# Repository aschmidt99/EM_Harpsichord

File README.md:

# NOTE: This repo is outdated!
Hello! While this repository still covers the basics of Lorentz Force Actuation and feedback, a more comprehensive and curated version can be found on this newer repository: [Sparksichord Project](https://github.com/aschmidt99/Sparksichord_NIME2025)

# Electromagnetic Harpsichord

The EM Harpsichord is an augmented harpsichord that uses optical sensors, audio power amplifier chips, and some simple signal processing to sustain the vibrations of its brass strings. This early prototype uses one circuit board for every string you wish to sustain. A work-in-progress performance/demonstration was given on October 2nd, 2023 at the 63rd Annual University of Michigan Organ Conference. For this demonstration, 3 strings had optical sustaining enabled and 8 strings had audio-playback enabled.

## Video Examples
Here is a [selection of audio examples](https://drive.google.com/drive/folders/1B2c4qz-7Rl1Y2wPH64m0Ud0_MTGL74a2?usp=sharing) of both sustainers and audio playback through the harpsichord strings.

## Working Principle
This simple board uses a ITR20403 Optical Photo-interrupt to sense the vibrations (position) of a harpsichord string. The derivative of this signal is amplified and sent to a 5-Watt audio amplifier chip (PAM8406) that is normally used to power small 4 or 8 ohm speakers. Rather than connect to a speaker, the output terminals of the speaker chip are connected to each end of one of the strings on a harpsichord. The amplified signal pushes current through the string, which generates an alternating magnetic field that interacts with a strong magnetic field from permanent neodymium magnets.

The working principle is similar to the more familiar eBow, but rather sensing and inducing vibrations with electromagnetic coils, we sense with an optical sensor and actuate with Lorentz force actuation.

## Simple System Diagram

This is the signal flow for the sustainer circuit in each board. You need one circuit board for each string you wish to sustain.

## The Circuit Board

The circuitboard is thin enough to fit between the harpsichord's strings. We mounted them to an aluminum extrusion C Beam with slide nuts, M4 screws, and some small 3D printed brackets.

## How to order
### JLCPCB
If you wish to have this exact board, you can order these circuit boards from JLCPCB by uploading GERBER-EMHarpsichord_Sustainer+Playback.zip to JLCPCB. Also upload BOM-EMHarpsichord_Sustainer+Playback.csv and CPL-EMHarpsichord_Sustainer+Playback.csv to have JLCPCB assemble the board for you.
(Note: Double check the orientation of each IC in JLCPCB. They are often incorrect by default.)

### Reach out to me
Alternatively, reach out to me (schmia@umich.edu) in case I have some extra :)

### Other board house
If you are familiar with a different board house, feel free to export as you usually would from KiCad.

### Notes before ordering/assembling
If you order based on my files, the optical sensor will be placed on the wrong side of the board. I found it easier to source the components from JLCPCB and desolder/resolder the ITR20403 to the other side of the board. If you can find them for cheap elsewhere, it would probably save you a small headache to order them separately and omit them from the board when ordering.

## How to use
### Wiring up
- A 3 Pin JST XH 2.54mm connector supplies 5V, Ground, and an auxiliary audio input. If you don't anticipate using audio playback, simply wire up the 5V and Ground and you are good to go. Chain several boards together to sustain multiple notes. We put a SPST switch between each board's ground and the power supply ground to allow us to select which strings were activated individually.
- The PAM8406 chip is advertised to support 4-8 ohm loads, though the data sheet notes that it can support loads down to 2 ohms. The data sheet also notes that outputs of the PAM8406 amplifier chip have built in short circuit protection, and the outputs will not activate if they detect less than 2 ohm load. Therefore, you must ensure that there are at least 2 ohms between the (+) and (-) terminal of each speaker output.
	- Most of the brass strings on our harpsichord measured much less than 1 Ohm, so we opted to put a 2-Ohm 10W Power Resistor between each string and one of the terminals the selected channels.

### Magnets
- To induce vibration, the strings must be exposed to a strong magnetic field. We have been using N52 neodymium magnets (purchased from kjmagnetics.com) for this purpose. The strength of the vibration is proportional to the strength of the magnetic field, and although the presence of just one or two magnets usually is enough to get sound going, more magnets seems to encourage a higher acoustic output.
- The orientation of the magnet does matter. Flip the magnet back and forth to determine which side is inducing the sound you like. One side should sustain the fundamental frequency of the string and the other may damp the fundamental while favoring odd harmonics.
- If you wish to use multiple magnets on a string, you will most likely want all of their poles pointed in the same direction, although interesting magnet placement can yield interesting results...

### Channels
- The 'left' output channel of the board is connected to the optical sensor, which creates a closed feedback loop to sustain vibrations on the connected string.
- The 'right' output channel of the board amplifies an auxiliary input signal.

### Additional Notes:
- The optical sensor needs to be placed very precisely over the string to ensure it picks up the vibration. The sensing range of the string is very small and is easy to clip. You can use an oscilloscope on test point 1 (TP1) to make sure the sensor isn't clipping before the gain stage.
- If it is clipping (and you do not like the output tone), consider moving the sensor board closer to a termination point of the string where its range of vibration is much smaller. This should yield a smoother sustaining sound.
- The feedback loop is very sensitive to the position of the sensor. You will likely notice timbral changes as you change the point on the string where the sensor is located, the position of the sensor over the string, and the positions of the magnets.
- Bar magnets induce stronger vibrations than cylindrical with the same pull force.
- The resistance of a metal string is a function of its material, gauge, length, and temperature. The higher the resistance, the more apt the string is to detuning. If your strings are detuning too much, try using a thicker wire, more conductive material, or lower current. If you are building a new instrument rather than augmenting an existing one, try different string lengths.

## Design References
- the 'RelevantDocuments' folder holds data sheets and some blog/forum posts I found helpful while designing the board. (Dave Corsie's blog)[https://www.davecorsie.com/optical-pickup-blog] helped me figure out how to design the optical pickup circuit and the DIYAudio blog helped me make a better PCB layout for the PAM8406 Chip.

## Future Improvements
### Support Loads < 2 Ohms
One of the most obvious shortcomings of this system is the wasted power. If a given string is only 0.2 Ohms and we compensate with a 2 Ohm resistor, most (~90%) of the power is being dissipated as heat through the resistor rather that contributing towards generating vibrations. I suspect looking into circuits that are anticipating extremely low loads such as ribbon speaker amplifiers will be a worthwhile endeavor and likely be a solution for the next version of this circuit.

### Lower Heat Buildup
On the other hand, the large dummy load ensures the majority of the power is dissipated somewhere other than the string, which prevents heat buildup (and thus detuning) in the string. The magnetic field generated by the string is proportional to current only - it does not factor in voltage. Therefore, an alternative system improvement may be to increase string gauges to /decrease/ overall resistance and continue to utilize the power resistors.

### Controlled Detuning
With more advanced feedback control, it may be possible to control how much or little each string is detuned during actuation. This could allow the performer to change tuning systems rapidly and on-the-fly - a process that usually takes considerable time and attention.

### Sustainer on every string
A natural progression for the project is to add a sustainer board for every string so that we can sustain any strings rather than just the few we chose for our work-in-progress demonstration. A double-manual harpsichord might work well, where one manual controls the sustainers and the other moves jacks and plucks the strings as usual.

### Sensing the keys
In the next version of this project, we aim to actively sense the position of each harpsichord key to use as a control signal for the sustainer of each corresponding string. Mechanically separating the harpsichord keys from the strings will allow us to map and re-map the interaction between key presses and actuation however we wish.

## Acknowledgements
- This project was enabled by Professor Joseph Gascho, Associate Professor of Music and Director of the Stearns Collection at the University of Michigan Ann Arbor.
- This project was inspired by the (Electromagnetic Resonator Piano)[http://instrumentslab.org/research/mrp.html], a project by Andrew McPherson at the Augmented Instruments Lab.
- Additional inspiration and insight was provided by (Techniques and Circuits for Electromagnetic Instrument Actuation)[https://www.nime.org/proceedings/2012/nime2012_117.pdf] by Andrew McPherson (see Section 2.4 - Lorentz Force Sustaining).

## Software Versions used
- KiCad (6.0.7-1)-1 for MaxOS Version 13.4.1
- LTSpice 17.0.40 for OS X

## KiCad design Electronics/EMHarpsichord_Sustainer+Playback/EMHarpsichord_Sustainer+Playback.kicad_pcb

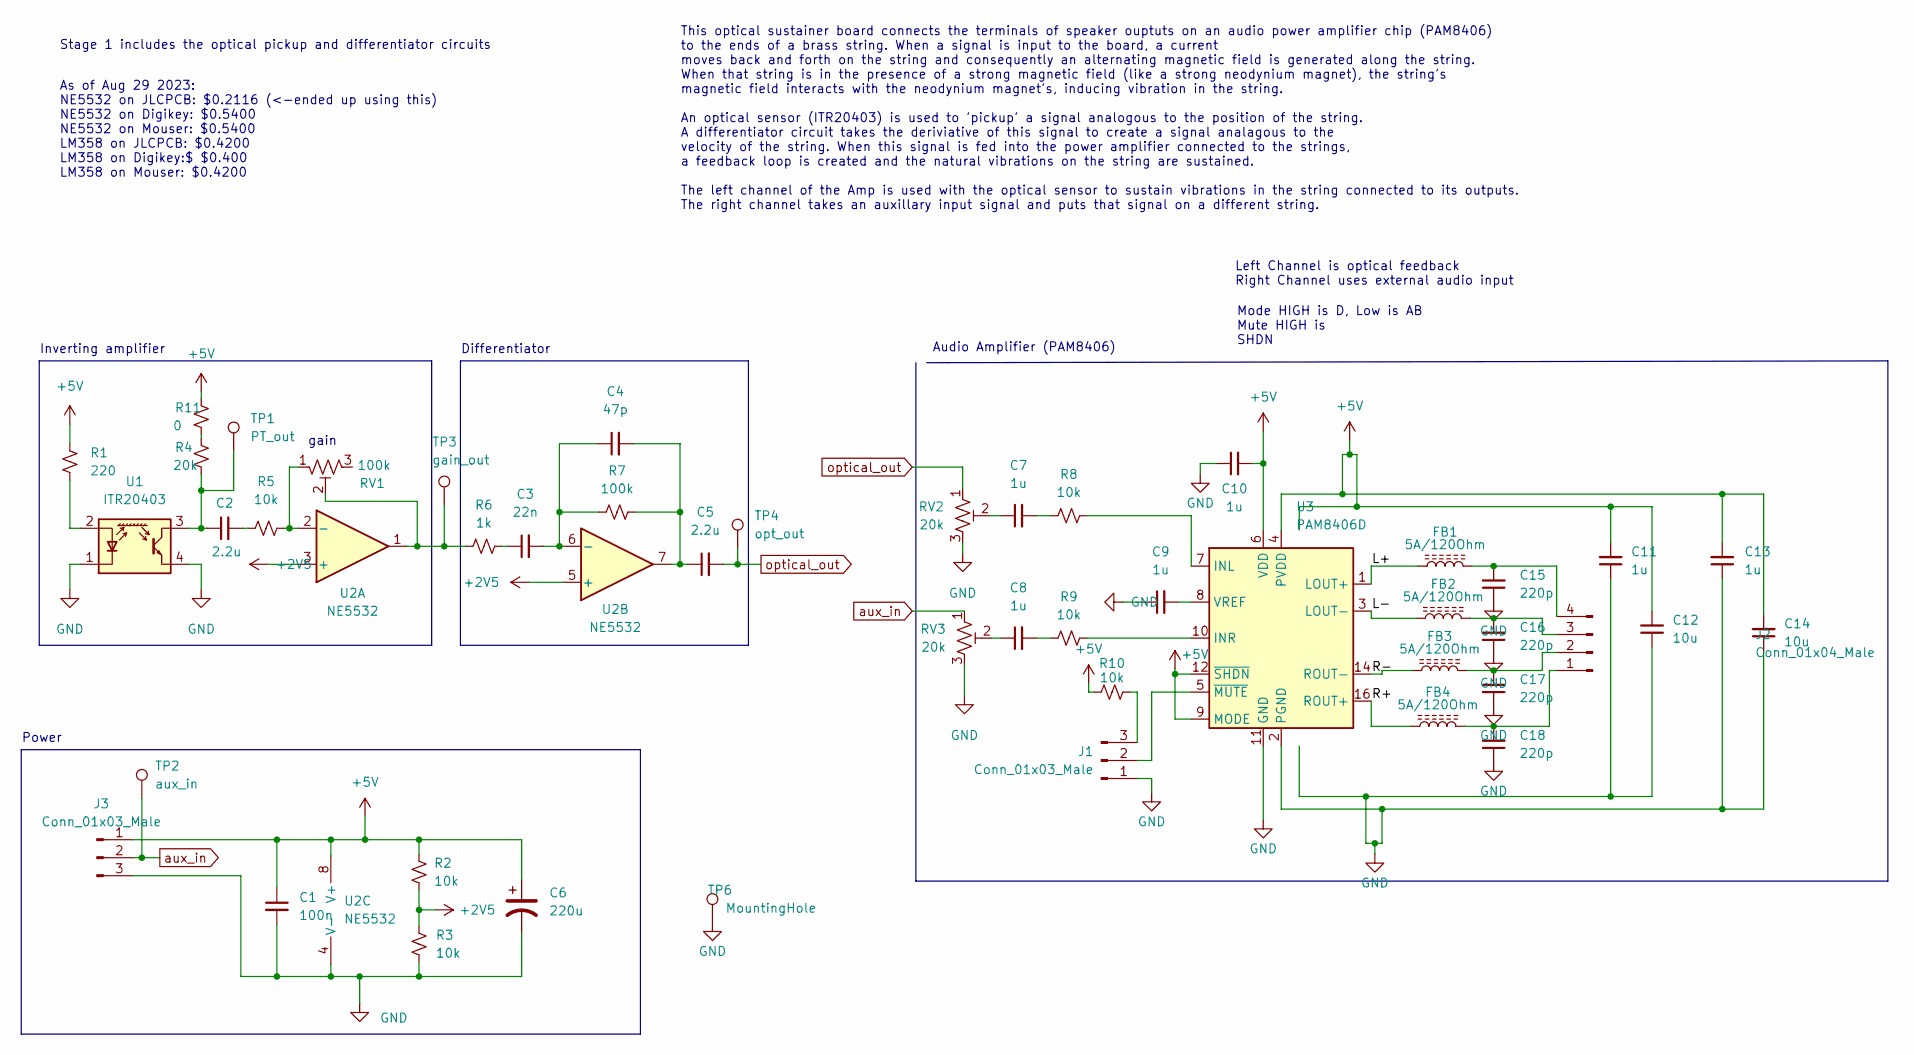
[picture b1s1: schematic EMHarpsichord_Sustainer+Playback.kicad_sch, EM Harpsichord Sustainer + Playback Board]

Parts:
C1: 100n; C_0603_1608Metric
C2, C5: 2.2u; C_0603_1608Metric
C3: 22n; C_0603_1608Metric
C4: 47p; C_0603_1608Metric
C6: 220u; C_Elec_6.3x5.8; LCSC C497579
C7, C8, C9, C10, C11, C13: 1u; C_0603_1608Metric; Rating 10V
C12, C14: 10u; C_0805_2012Metric; Rating 10V
C15, C16, C17, C18: 220p; C_0603_1608Metric; Rating 10V
FB1, FB2, FB3, FB4: 5A/120Ohm; C_0805_2012Metric; LCSC C304323
J1: Conn_01x03_Male; PinHeader_1x03_P2.54mm_Vertical; LCSC C2914353
J2: Conn_01x04_Male; PinHeader_1x04_P2.54mm_Vertical
J3: Conn_01x03_Male; JST_XH_B3B-XH-A_1x03_P2.50mm_Vertical; LCSC C161870
R1: 220; R_0603_1608Metric
R2, R3, R5, R8, R9, R10: 10k; R_0603_1608Metric
R4: 20k; R_0603_1608Metric
R6: 1k; R_0603_1608Metric
R7: 100k; R_0603_1608Metric
R11: 0; R_0603_1608Metric
RV1: 100k; Potentiometer_Bourns_3224J_Horizontal; LCSC C719185
RV2: 20k; Potentiometer_Bourns_3224J_Horizontal; LCSC C719181
RV3: 20k; Potentiometer_Bourns_3224J_Horizontal; LCSC C719185
TP1: PT_out; TestPoint_THTPad_D2.0mm_Drill1.0mm
TP2: aux_in; TestPoint_THTPad_D2.0mm_Drill1.0mm
TP3: gain_out; TestPoint_THTPad_D2.0mm_Drill1.0mm
TP4: opt_out; TestPoint_THTPad_D2.0mm_Drill1.0mm
TP6: MountingHole; TestPoint_THTPad_D2.0mm_Drill1.0mm
U1: ITR20403; Everlight_ITR20403; LCSC C5135
U2: NE5532; SOP-8_3.76x4.96mm_P1.27mm; LCSC C7426
U3: PAM8406D; SOP-16_3.9x9.9mm_P1.27mm; LCSC C86270

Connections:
+2V5: R2.1, R3.2, U2.3 (+), U2.5 (+)
+5V: C1.1, C6.1, C10.2, C11.2, C12.2, C13.2, C14.2, J3.1, R1.1, R2.2, R10.1, R11.1, U2.8 (V+), U3.4 (PVDD), U3.6 (VDD), U3.9 (MODE), U3.12 (~SHDN), U3.13 (PVDD)
/L+: FB1.1, U3.1 (LOUT+)
/L-: FB2.1, U3.3 (LOUT-)
/R+: FB4.1, U3.16 (ROUT+)
/R-: FB3.1, U3.14 (ROUT-)
GND: C1.2, C6.2, C9.1, C10.1, C11.1, C12.1, C13.1, C14.1, C15.1, C16.1, C17.1, C18.1, J1.1, J3.3, R3.1, RV2.3, RV3.3, TP6.1, U1.1 (K), U1.4 (E), U2.4 (V-), U3.2 (PGND), U3.11 (GND), U3.15 (PGND)
unnamed: C2.1, R4.2, TP1.1, U1.3 (C)
unnamed: C2.2, R5.1
unnamed: C3.1, R6.2
unnamed: C3.2, C4.1, R7.1, U2.6 (-)
unnamed: C4.2, C5.1, R7.2, U2.7
unnamed: C7.1, RV2.2
unnamed: C7.2, R8.1
unnamed: C8.1, RV3.2
unnamed: C8.2, R9.1
unnamed: C9.2, U3.8 (VREF)
unnamed: C15.2, FB1.2, J2.4
unnamed: C16.2, FB2.2, J2.3
unnamed: C17.2, FB3.2, J2.2
unnamed: C18.2, FB4.2, J2.1
unnamed: R1.2, U1.2 (A)
unnamed: R5.2, RV1.1, U2.2 (-)
unnamed: R6.1, RV1.2, TP3.1, U2.1
unnamed: R8.2, U3.7 (INL)
unnamed: R9.2, U3.10 (INR)
unnamed: J1.3, R10.2
unnamed: R4.1, R11.2
unnamed: J1.2, U3.5 (~MUTE)
aux_in: J3.2, RV3.1, TP2.1
optical_out: C5.2, RV2.1, TP4.1

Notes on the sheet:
Left Channel is optical feedback Right Channel uses external audio input
Power
This optical sustainer board connects the terminals of speaker ouptuts on an audio power amplifier chip (PAM8406) to the ends of a brass string. When a signal is input to the board, a current moves back and forth on the string and consequently an alternating magnetic field is generated along the st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
Audio Amplifier (PAM8406)
Mode HIGH is D, Low is AB Mute HIGH is SHDN
Differentiator
As of Aug 29 2023: NE5532 on JLCPCB: $0.2116 (<-ended up using this) NE5532 on Digikey: $0.5400 NE5532 on Mouser: $0.5400 LM358 on JLCPCB: $0.4200 LM358 on Digikey:$ $0.400 LM358 on Mouser: $0.4200
Inverting amplifier
gain
Stage 1 includes the optical pickup and differentiator circuits

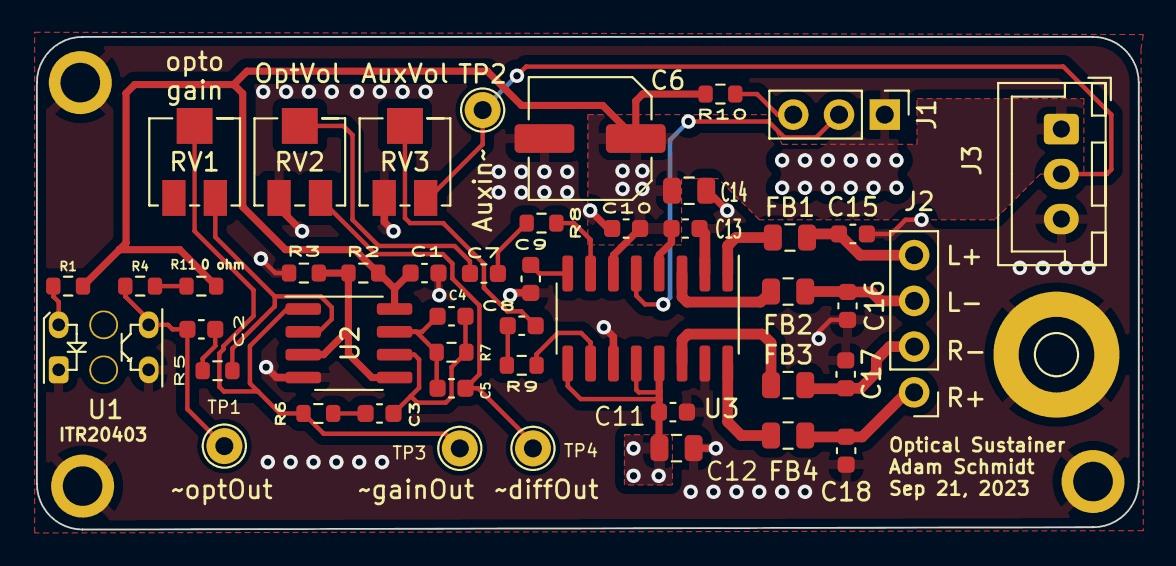
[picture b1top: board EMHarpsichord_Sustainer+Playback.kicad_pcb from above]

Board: 2 copper layers, 61.2 x 27.4 mm, 47 parts (0 on the bottom side), 31 nets.

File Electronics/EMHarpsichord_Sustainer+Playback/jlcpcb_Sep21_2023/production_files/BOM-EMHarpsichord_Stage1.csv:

Comment,Designator,Footprint,LCSC
Conn_01x03_Male,J3,JST_XH_B3B-XH-A_1x03_P2.50mm_Vertical,C161870
220u,C6,C_Elec_6.3x5.8,C497579
ITR20403,U1,Everlight_ITR20403,C5135
20k,RV2,Potentiometer_Bourns_3224J_Horizontal,C719181
100k,"RV1,RV3",Potentiometer_Bourns_3224J_Horizontal,C719185
NE5532,U2,SOP-8_3.76x4.96mm_P1.27mm,C7426
PAM8406D,U3,SOP-16_3.9x9.9mm_P1.27mm,C86270
opt_out,TP4,TestPoint_THTPad_D2.0mm_Drill1.0mm,
2.2u,C2,C_0603_1608Metric,
20k,R4,R_0603_1608Metric,
0,R11,R_0603_1608Metric,
Conn_01x04_Male,J2,PinHeader_1x04_P2.54mm_Vertical,
5A/120Ohm,FB3,C_0805_2012Metric,
22n,C3,C_0603_1608Metric,
PT_out,TP1,TestPoint_THTPad_D2.0mm_Drill1.0mm,
220p,C17,C_0603_1608Metric,
Conn_01x03_Male,J1,PinHeader_1x03_P2.54mm_Vertical,
10k,R2,R_0603_1608Metric,
10k,R10,R_0603_1608Metric,
1u,C7,C_0603_1608Metric,
2.2u,C5,C_0603_1608Metric,
gain_out,TP3,TestPoint_THTPad_D2.0mm_Drill1.0mm,
5A/120Ohm,FB4,C_0805_2012Metric,
10k,R5,R_0603_1608Metric,
1u,C9,C_0603_1608Metric,
1k,R6,R_0603_1608Metric,
220p,C18,C_0603_1608Metric,
1u,C11,C_0603_1608Metric,
220p,C15,C_0603_1608Metric,
1u,C13,C_0603_1608Metric,
100n,C1,C_0603_1608Metric,
220p,C16,C_0603_1608Metric,
1u,C10,C_0603_1608Metric,
220,R1,R_0603_1608Metric,
1u,C8,C_0603_1608Metric,
5A/120Ohm,FB1,C_0805_2012Metric,
10u,C12,C_0805_2012Metric,
10k,R3,R_0603_1608Metric,
100k,R7,R_0603_1608Metric,
10u,C14,C_0805_2012Metric,
MountingHole,TP6,TestPoint_THTPad_D2.0mm_Drill1.0mm,
5A/120Ohm,FB2,C_0805_2012Metric,
10k,R8,R_0603_1608Metric,
10k,R9,R_0603_1608Metric,
aux_in,TP2,TestPoint_THTPad_D2.0mm_Drill1.0mm,
47p,C4,C_0603_1608Metric,

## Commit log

2023-12-12 initial commit to github
    Organizing EM Harpsichord files:
    On github: CAD, Code, Electronics, some images
    offline: receipts, most audio files, videos
2023-12-12 Reorganizing and Naming files
2023-12-12 More tidying files and adding comments to schematics
2023-12-12 updating the readme
    also renamed some files
2023-12-12 readme.md
2023-12-12 Incorporating Photos to ReadMe
2023-12-12 Almost done
2023-12-12 testing new images
2023-12-12 testing again
2023-12-13 Updating Readme
2023-12-13 Adding Demos
2025-04-20 Linking Updated Repo: Sparksichord_NIME2025
    This is now an outdated project and has been replaced by the following repo: https://github.com/aschmidt99/Sparksichord_NIME2025
